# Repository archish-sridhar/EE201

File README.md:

# Archish Sridhar
Hello my name is Archish Sridhar and this is my personal webpage. 
### About me
I was born in Toronto, Canada and have lived in Wisconsin for most of my life. I moved to Washington in sophomore year of high school and currently am a Junior in ECE at the University of Washington. Thanks for reading my page!

I ranked my favorite favorite colors
1. Sage Green
2. Maroon
3. Cyan

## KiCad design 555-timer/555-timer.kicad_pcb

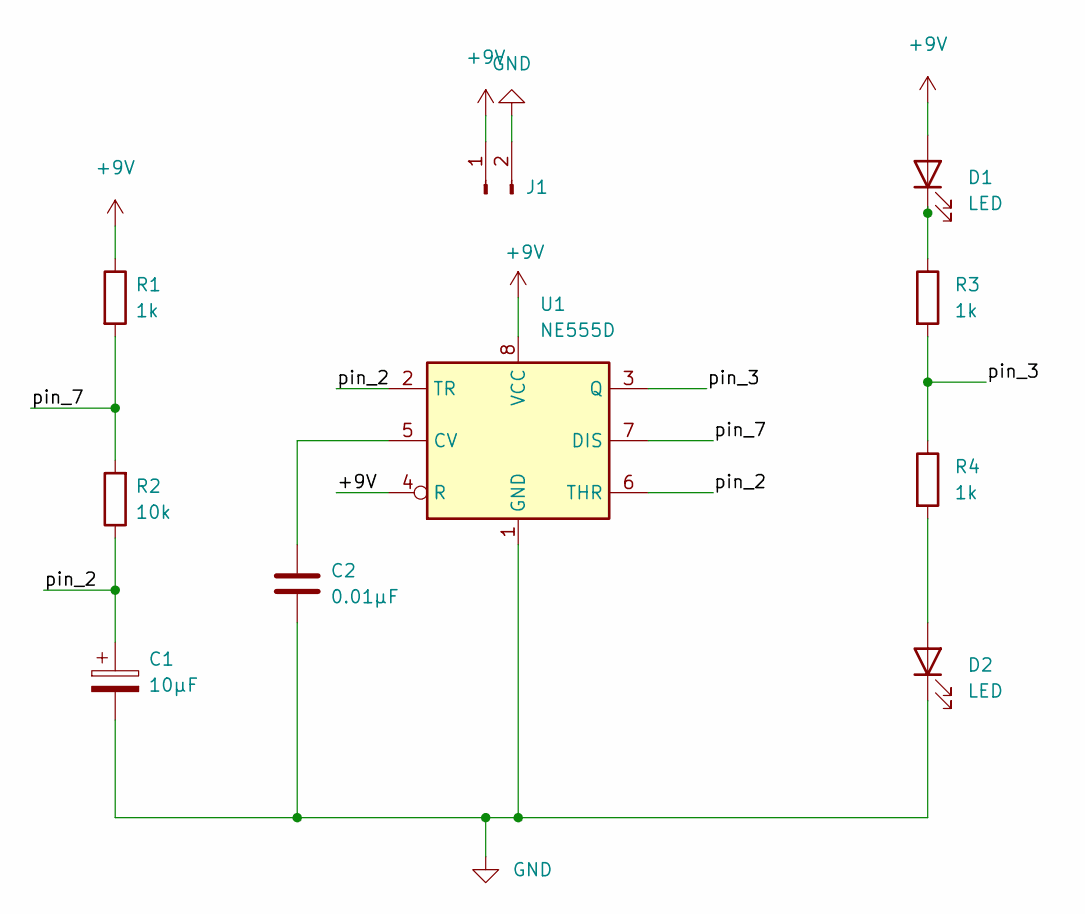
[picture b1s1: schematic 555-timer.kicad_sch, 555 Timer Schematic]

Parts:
C1: 10µF; CP_EIA-3216-18_Kemet-A_Pad1.58x1.35mm_HandSolder
C2: 0.01µF; C_0805_2012Metric_Pad1.18x1.45mm_HandSolder
D1, D2: LED; LED_1206_3216Metric_Pad1.42x1.75mm_HandSolder
J1: Conn_01x02_Male; JST_EH_S2B-EH_1x02_P2.50mm_Horizontal
R1, R3, R4: 1k; R_0805_2012Metric_Pad1.20x1.40mm_HandSolder
R2: 10k; R_0805_2012Metric_Pad1.20x1.40mm_HandSolder
U1: NE555D; SOIC-8-1EP_3.9x4.9mm_P1.27mm_EP2.29x3mm

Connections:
+9V: D1.2 (A), J1.1, R1.1, U1.4 (R), U1.8 (VCC)
/pin_2: C1.1, R2.1, U1.2 (TR), U1.6 (THR)
/pin_3: R3.2, R4.1, U1.3 (Q)
/pin_7: R1.2, R2.2, U1.7 (DIS)
GND: C1.2, C2.2, D2.1 (K), J1.2, U1.1 (GND)
unnamed: C2.1, U1.5 (CV)
unnamed: D1.1 (K), R3.1
unnamed: D2.2 (A), R4.2

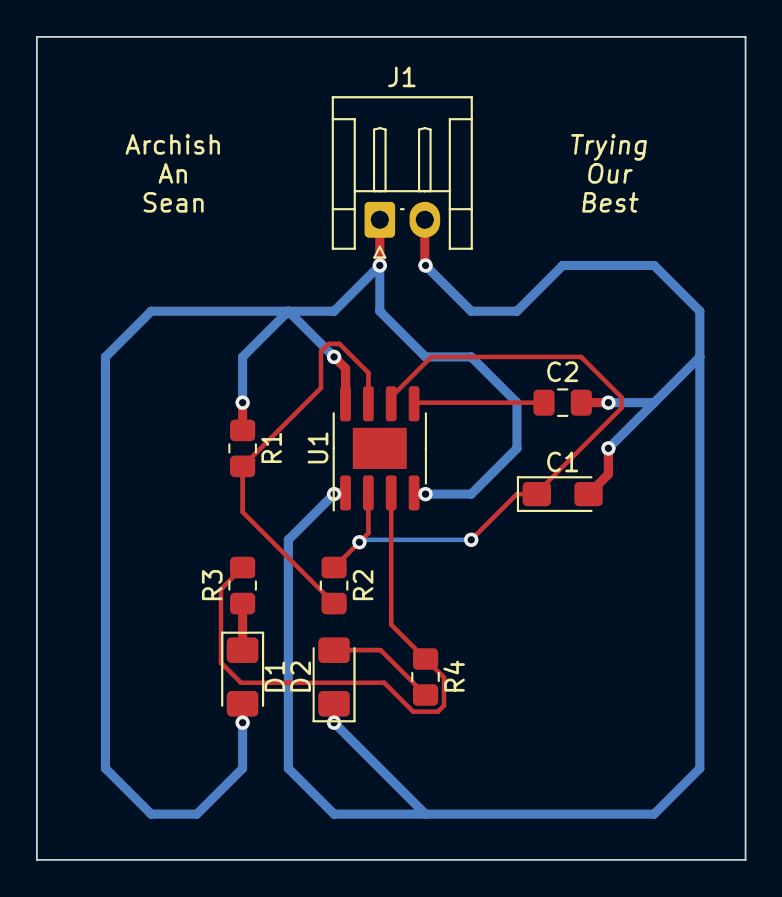
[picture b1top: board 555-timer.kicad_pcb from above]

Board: 2 copper layers, 39.4 x 45.7 mm, 10 parts (0 on the bottom side), 8 nets.

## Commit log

2023-04-04 ALL G
2023-04-04 AHHHH WHAT IS IT DOING NO NO STOP STOO
2023-04-07 555 Timer Schem
2023-04-14 this work?
2023-04-14 AAAAAAAAAAAAAAAAAAAAAAAAAH
2023-04-21 This is the FreeCAD file update
2023-05-02 Arduino code fiels
2023-05-09 Soldering Project Files
